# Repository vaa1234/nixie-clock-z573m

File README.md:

Nixie Clock on z573m tubes, hv5222 and raspberry pi.

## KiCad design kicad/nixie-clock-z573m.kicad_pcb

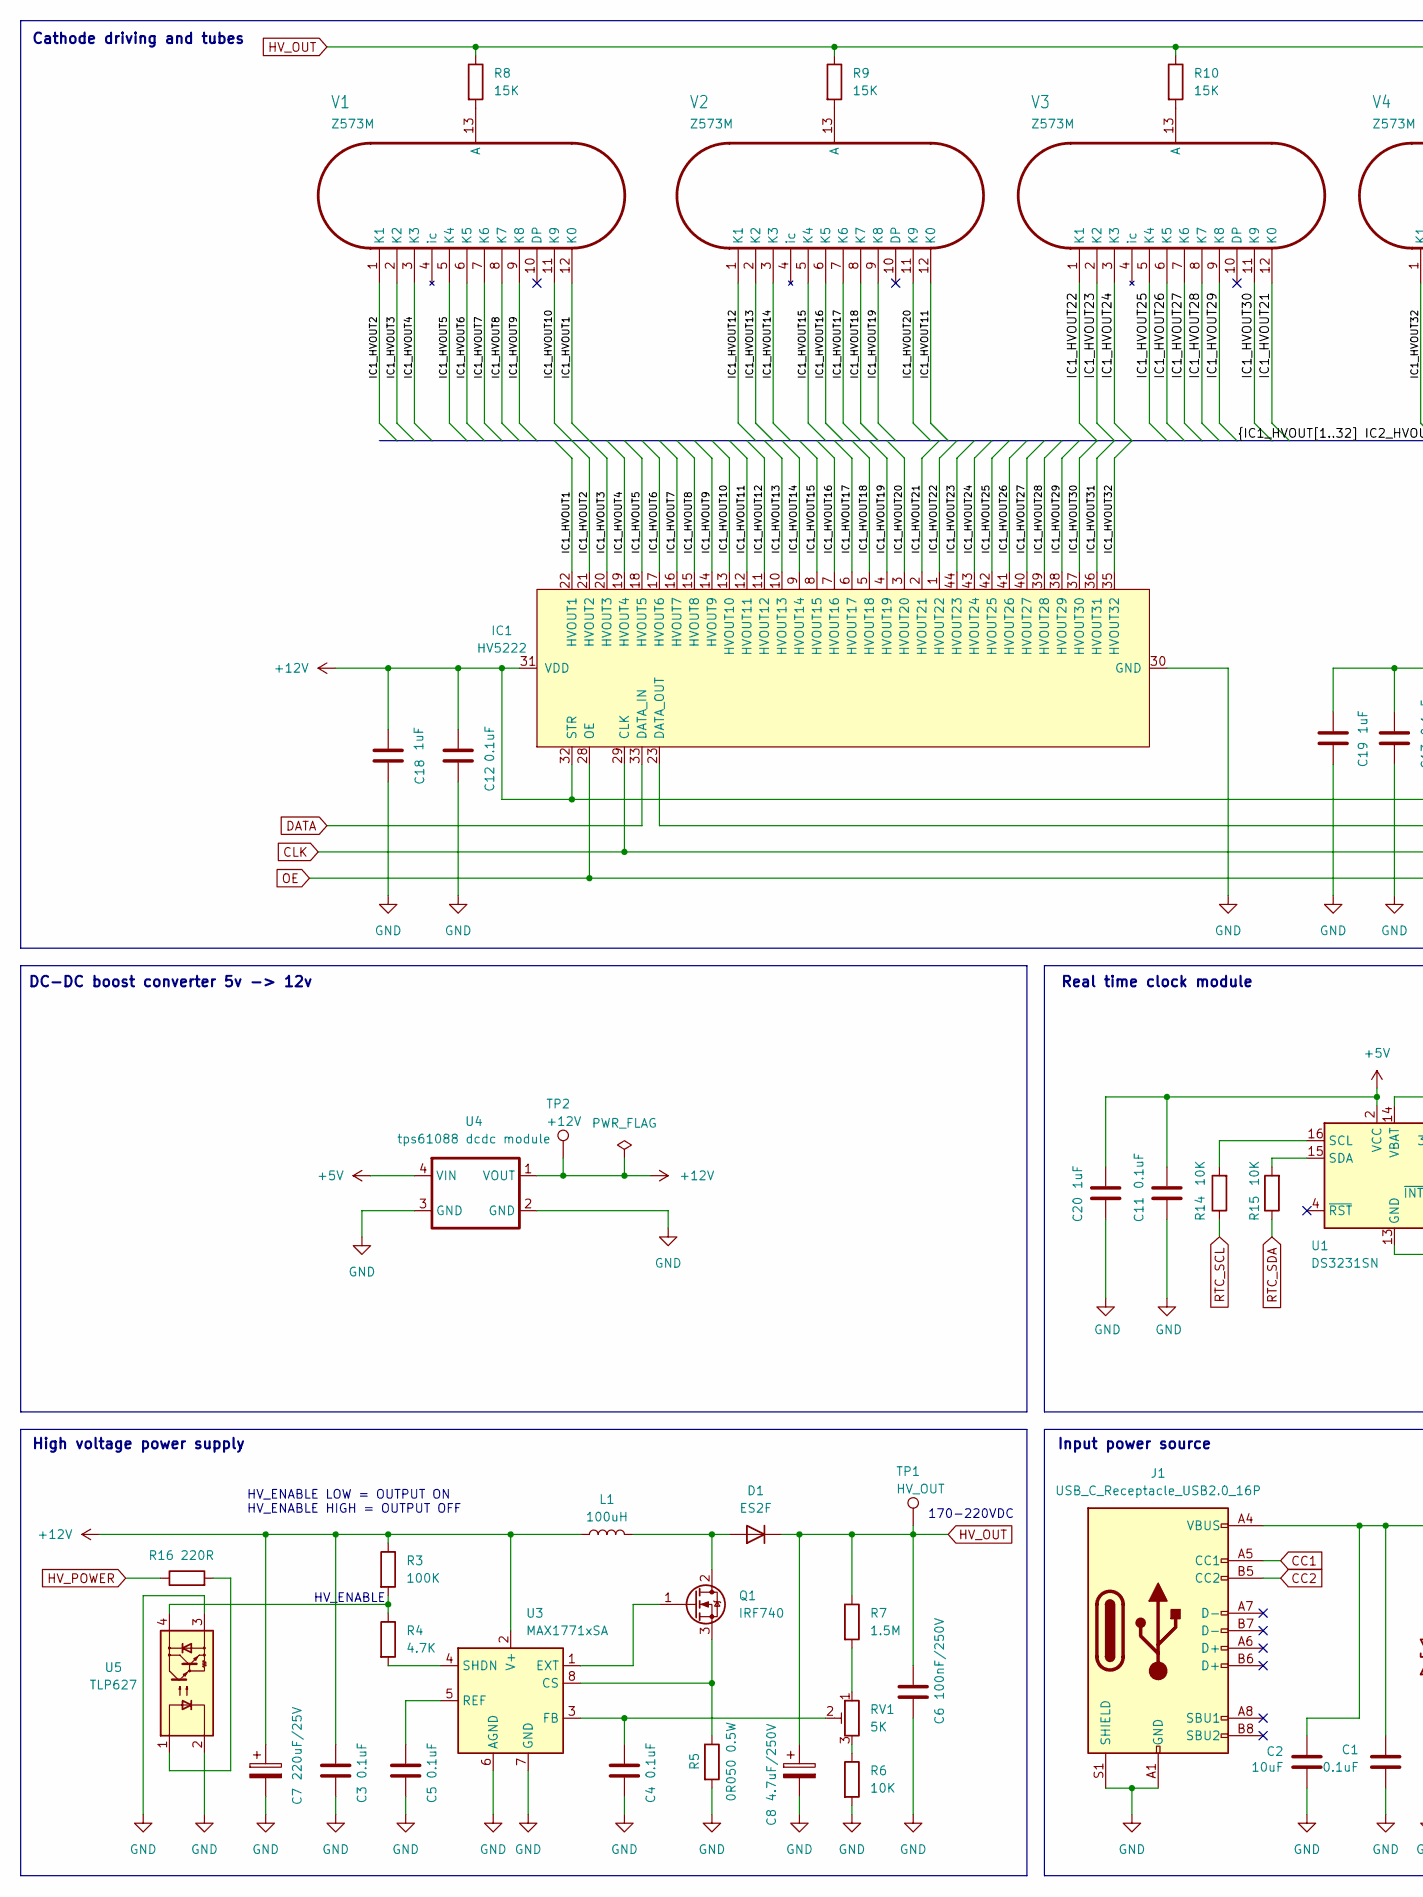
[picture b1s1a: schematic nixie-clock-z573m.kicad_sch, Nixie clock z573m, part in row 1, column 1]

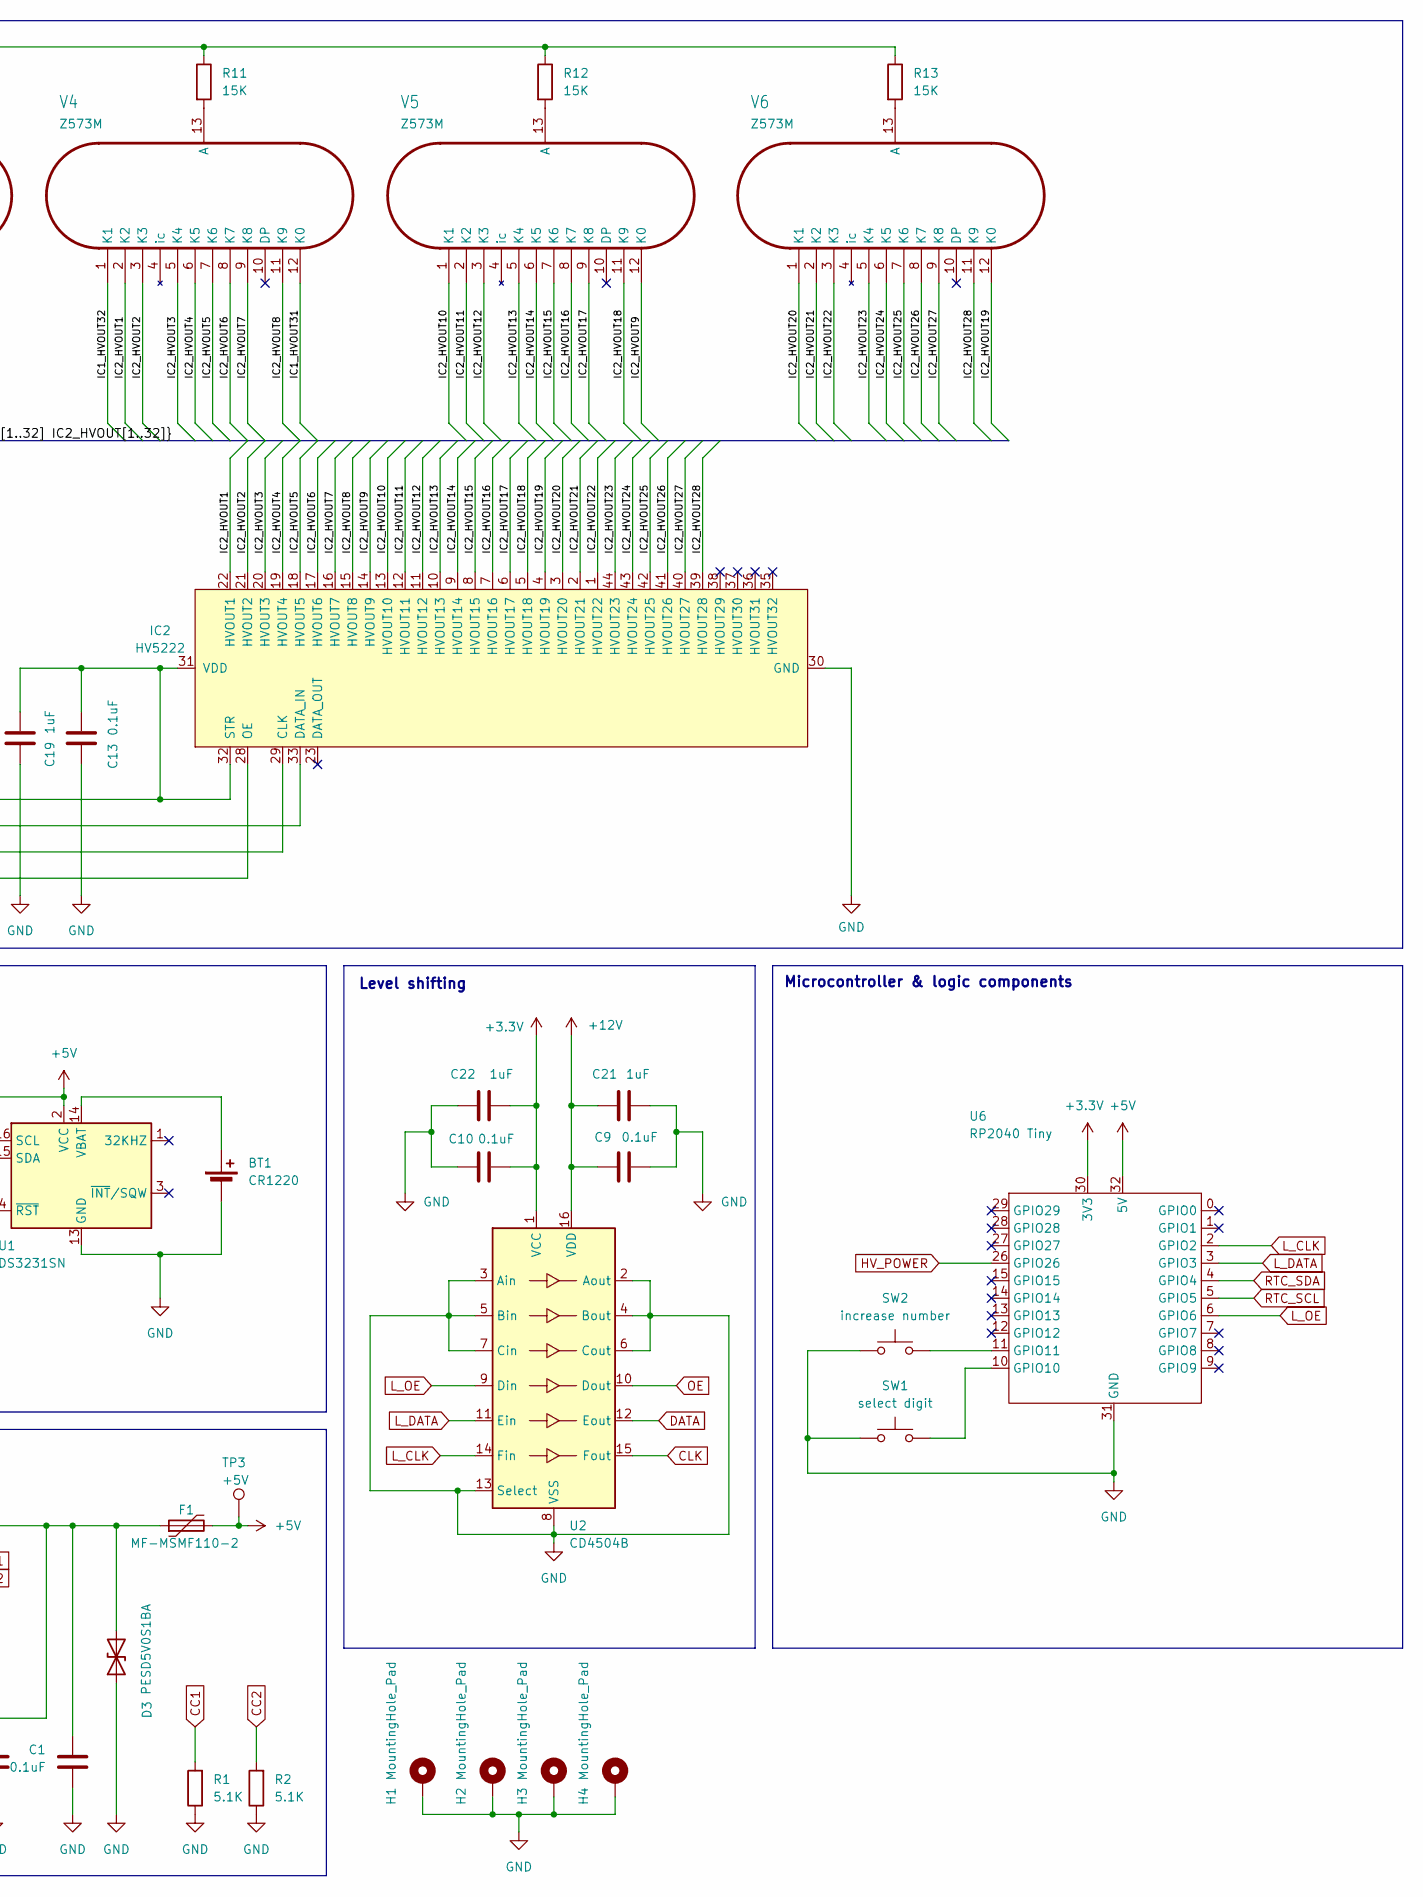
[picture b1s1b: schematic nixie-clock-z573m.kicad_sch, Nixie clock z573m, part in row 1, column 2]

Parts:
BT1: CR1220; BatteryHolder_Keystone_3000_1x12mm
C1, C3, C4, C5, C9, C10, C11, C12, C13: 0.1uF; C_0402_1005Metric_Pad0.74x0.62mm_HandSolder
C2: 10uF; C_0805_2012Metric_Pad1.18x1.45mm_HandSolder
C6: 100nF/250V; C_1206_3216Metric_Pad1.33x1.80mm_HandSolder
C7: 220uF/25V; CP_Elec_8x10.5
C8: 4.7uF/250V; CP_Elec_8x10
C18, C19, C20, C21, C22: 1uF; C_0201_0603Metric_Pad0.64x0.40mm_HandSolder
D1: ES2F; D_SMB_Handsoldering
D3: PESD5V0S1BA; D_SOD-323
F1: MF-MSMF110-2; Fuse_1812_4532Metric_Pad1.30x3.40mm_HandSolder
H1, H2, H3, H4: MountingHole_Pad; MountingHole_3mm_Pad_Via
IC1, IC2: HV5222; PQFP-44_10x10mm_P0.8mm
J1: USB_C_Receptacle_USB2.0_16P; USB_C_Receptacle_GCT_USB4105-xx-A_16P_TopMnt_Horizontal
L1: 100uH; L_12x12mm_H8mm
Q1: IRF740; TO-252-2
R1, R2: 5.1K; R_0402_1005Metric_Pad0.72x0.64mm_HandSolder
R3: 100K; R_0603_1608Metric_Pad0.98x0.95mm_HandSolder
R4: 4.7K; R_0603_1608Metric_Pad0.98x0.95mm_HandSolder
R5: 0R050 0.5W; R_2010_5025Metric_Pad1.40x2.65mm_HandSolder
R6: 10K; R_0603_1608Metric_Pad0.98x0.95mm_HandSolder
R7: 1.5M; R_0603_1608Metric_Pad0.98x0.95mm_HandSolder
R8, R9, R10, R11, R12, R13: 15K; R_1206_3216Metric_Pad1.30x1.75mm_HandSolder
R14, R15: 10K; R_0201_0603Metric_Pad0.64x0.40mm_HandSolder
R16: 220R; R_0603_1608Metric_Pad0.98x0.95mm_HandSolder
RV1: 5K; Potentiometer_Bourns_3224W_Vertical
SW1: select digit; SW_Tactile_SPST_Angled_PTS645Vx83-2LFS
SW2: increase number; SW_Tactile_SPST_Angled_PTS645Vx83-2LFS
TP1: HV_OUT; TestPoint_Pad_D1.0mm
TP2: +12V; TestPoint_Pad_D1.0mm
TP3: +5V; TestPoint_Pad_D1.0mm
U1: DS3231SN; SOIC-16W_7.5x10.3mm_P1.27mm
U2: CD4504B; SOIC-16W_5.3x10.2mm_P1.27mm
U3: MAX1771xSA; SO-8_3.9x4.9mm_P1.27mm
U4: tps61088 dcdc module; tps61088_module
U5: TLP627; DIP-4_W7.62mm_Socket
U6: RP2040 Tiny; RP2040-Tiny_SMD
V1, V2, V3, V4, V5, V6: Z573M; Z573M_SMD

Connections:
+3.3V: C10.2, C22.2, U2.1 (VCC), U6.30 (3V3)
+5V: C11.1, C20.1, F1.2, TP3.1, U1.2 (VCC), U4.4 (VIN), U6.32 (5V)
+12V: C3.1, C7.1, C9.1, C12.1, C13.1, C18.1, C19.1, C21.1, IC1.31 (VDD), IC1.32 (STR), IC2.31 (VDD), IC2.32 (STR), L1.1, R3.1, TP2.1, U2.16 (VDD), U3.2 (V+), U4.1 (VOUT)
/IC1_HVOUT1: IC1.22 (HVOUT1), V1.12 (K0)
/IC1_HVOUT2: IC1.21 (HVOUT2), V1.1 (K1)
/IC1_HVOUT3: IC1.20 (HVOUT3), V1.2 (K2)
/IC1_HVOUT4: IC1.19 (HVOUT4), V1.3 (K3)
/IC1_HVOUT5: IC1.18 (HVOUT5), V1.5 (K4)
/IC1_HVOUT6: IC1.17 (HVOUT6), V1.6 (K5)
/IC1_HVOUT7: IC1.16 (HVOUT7), V1.7 (K6)
/IC1_HVOUT8: IC1.15 (HVOUT8), V1.8 (K7)
/IC1_HVOUT9: IC1.14 (HVOUT9), V1.9 (K8)
/IC1_HVOUT10: IC1.13 (HVOUT10), V1.11 (K9)
/IC1_HVOUT11: IC1.12 (HVOUT11), V2.12 (K0)
/IC1_HVOUT12: IC1.11 (HVOUT12), V2.1 (K1)
/IC1_HVOUT13: IC1.10 (HVOUT13), V2.2 (K2)
/IC1_HVOUT14: IC1.9 (HVOUT14), V2.3 (K3)
/IC1_HVOUT15: IC1.8 (HVOUT15), V2.5 (K4)
/IC1_HVOUT16: IC1.7 (HVOUT16), V2.6 (K5)
/IC1_HVOUT17: IC1.6 (HVOUT17), V2.7 (K6)
/IC1_HVOUT18: IC1.5 (HVOUT18), V2.8 (K7)
/IC1_HVOUT19: IC1.4 (HVOUT19), V2.9 (K8)
/IC1_HVOUT20: IC1.3 (HVOUT20), V2.11 (K9)
/IC1_HVOUT21: IC1.2 (HVOUT21), V3.12 (K0)
/IC1_HVOUT22: IC1.1 (HVOUT22), V3.1 (K1)
/IC1_HVOUT23: IC1.44 (HVOUT23), V3.2 (K2)
/IC1_HVOUT24: IC1.43 (HVOUT24), V3.3 (K3)
/IC1_HVOUT25: IC1.42 (HVOUT25), V3.5 (K4)
/IC1_HVOUT26: IC1.41 (HVOUT26), V3.6 (K5)
/IC1_HVOUT27: IC1.40 (HVOUT27), V3.7 (K6)
/IC1_HVOUT28: IC1.39 (HVOUT28), V3.8 (K7)
/IC1_HVOUT29: IC1.38 (HVOUT29), V3.9 (K8)
/IC1_HVOUT30: IC1.37 (HVOUT30), V3.11 (K9)
/IC1_HVOUT31: IC1.36 (HVOUT31), V4.12 (K0)
/IC1_HVOUT32: IC1.35 (HVOUT32), V4.1 (K1)
/IC2_HVOUT1: IC2.22 (HVOUT1), V4.2 (K2)
/IC2_HVOUT2: IC2.21 (HVOUT2), V4.3 (K3)
/IC2_HVOUT3: IC2.20 (HVOUT3), V4.5 (K4)
/IC2_HVOUT4: IC2.19 (HVOUT4), V4.6 (K5)
/IC2_HVOUT5: IC2.18 (HVOUT5), V4.7 (K6)
/IC2_HVOUT6: IC2.17 (HVOUT6), V4.8 (K7)
/IC2_HVOUT7: IC2.16 (HVOUT7), V4.9 (K8)
/IC2_HVOUT8: IC2.15 (HVOUT8), V4.11 (K9)
/IC2_HVOUT9: IC2.14 (HVOUT9), V5.12 (K0)
/IC2_HVOUT10: IC2.13 (HVOUT10), V5.1 (K1)
/IC2_HVOUT11: IC2.12 (HVOUT11), V5.2 (K2)
/IC2_HVOUT12: IC2.11 (HVOUT12), V5.3 (K3)
/IC2_HVOUT13: IC2.10 (HVOUT13), V5.5 (K4)
/IC2_HVOUT14: IC2.9 (HVOUT14), V5.6 (K5)
/IC2_HVOUT15: IC2.8 (HVOUT15), V5.7 (K6)
/IC2_HVOUT16: IC2.7 (HVOUT16), V5.8 (K7)
/IC2_HVOUT17: IC2.6 (HVOUT17), V5.9 (K8)
/IC2_HVOUT18: IC2.5 (HVOUT18), V5.11 (K9)
/IC2_HVOUT19: IC2.4 (HVOUT19), V6.12 (K0)
/IC2_HVOUT20: IC2.3 (HVOUT20), V6.1 (K1)
/IC2_HVOUT21: IC2.2 (HVOUT21), V6.2 (K2)
/IC2_HVOUT22: IC2.1 (HVOUT22), V6.3 (K3)
/IC2_HVOUT23: IC2.44 (HVOUT23), V6.5 (K4)
/IC2_HVOUT24: IC2.43 (HVOUT24), V6.6 (K5)
/IC2_HVOUT25: IC2.42 (HVOUT25), V6.7 (K6)
/IC2_HVOUT26: IC2.41 (HVOUT26), V6.8 (K7)
/IC2_HVOUT27: IC2.40 (HVOUT27), V6.9 (K8)
/IC2_HVOUT28: IC2.39 (HVOUT28), V6.11 (K9)
CC1: J1.A5 (CC1), R1.2
CC2: J1.B5 (CC2), R2.2
CLK: IC1.29 (CLK), IC2.29 (CLK), U2.15 (Fout)
DATA: IC1.33 (DATA_IN), U2.12 (Eout)
GND: BT1.2 (-), C1.2, C2.1, C3.2, C4.2, C5.2, C6.2, C7.2, C8.2, C9.2, C10.1, C11.2, C12.2, C13.2, C18.2, C19.2, C20.2, C21.2, C22.1, D3.1 (A1), H1.1, H2.1, H3.1, H4.1, IC1.30 (GND), IC2.30 (GND), J1.A1 (GND), J1.A12 (GND), J1.B1 (GND), J1.B12 (GND), J1.S1 (SHIELD), R1.1, R2.1, R5.2, R6.2, SW1.1, SW2.1, U1.5 (GND), U1.6 (GND), U1.7 (GND), U1.8 (GND), U1.9 (GND), U1.10 (GND), U1.11 (GND), U1.12 (GND), U1.13 (GND), U2.2 (Aout), U2.3 (Ain), U2.4 (Bout), U2.5 (Bin), U2.6 (Cout), U2.7 (Cin), U2.8 (VSS), U2.13 (Select), U3.6 (AGND), U3.7 (GND), U4.2 (GND), U4.3 (GND), U5.2, U5.3, U6.31 (GND)
HV_OUT: C6.1, C8.1, D1.1 (K), R7.1, R8.1, R9.1, R10.1, R11.1, R12.1, R13.1, TP1.1
HV_POWER: R16.1, U6.26 (GPIO26)
L_CLK: U2.14 (Fin), U6.2 (GPIO2)
L_DATA: U2.11 (Ein), U6.3 (GPIO3)
L_OE: U2.9 (Din), U6.6 (GPIO6)
unnamed: BT1.1 (+), U1.14 (VBAT)
unnamed: D1.2 (A), L1.2, Q1.2 (D)
unnamed: C1.1, C2.2, D3.2 (A2), F1.1, J1.A4 (VBUS), J1.A9 (VBUS), J1.B4 (VBUS), J1.B9 (VBUS)
unnamed: IC1.23 (DATA_OUT), IC2.33 (DATA_IN)
unnamed: Q1.1 (G), U3.1 (EXT)
unnamed: Q1.3 (S), R5.1, U3.8 (CS)
unnamed: R3.2, R4.1, U5.4
unnamed: R6.1, RV1.3
unnamed: R7.2, RV1.1
unnamed: R16.2, U5.1
unnamed: R14.2, U1.16 (SCL)
unnamed: R15.2, U1.15 (SDA)
unnamed: C4.1, RV1.2, U3.3 (FB)
unnamed: C5.1, U3.5 (REF)
unnamed: R4.2, U3.4 (SHDN)
unnamed: SW1.2, U6.10 (GPIO10)
unnamed: SW2.2, U6.11 (GPIO11)
unnamed: R8.2, V1.13 (A)
unnamed: R9.2, V2.13 (A)
unnamed: R10.2, V3.13 (A)
unnamed: R11.2, V4.13 (A)
unnamed: R12.2, V5.13 (A)
unnamed: R13.2, V6.13 (A)
OE: IC1.28 (OE), IC2.28 (OE), U2.10 (Dout)
RTC_SCL: R14.1, U6.5 (GPIO5)
RTC_SDA: R15.1, U6.4 (GPIO4)

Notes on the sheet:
Level shifting
High voltage power supply
Real time clock module
HV_ENABLE LOW = OUTPUT ON HV_ENABLE HIGH = OUTPUT OFF
Input power source
Microcontroller & logic components
Cathode driving and tubes
170-220VDC
HV_ENABLE
DC-DC boost converter 5v -> 12v

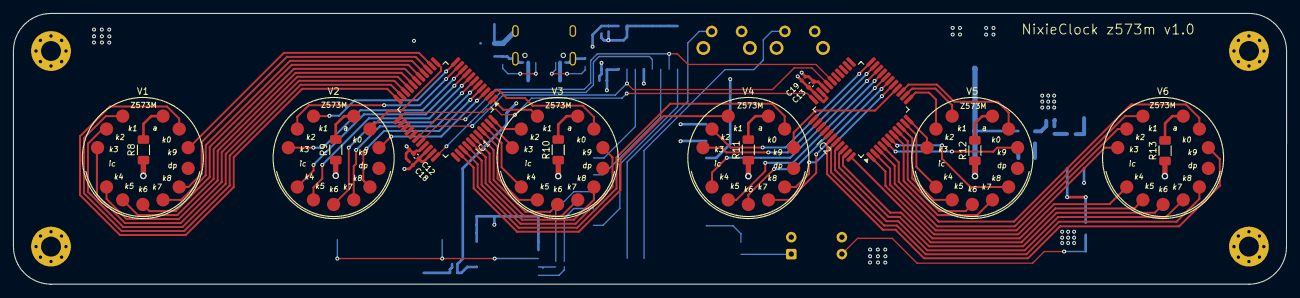
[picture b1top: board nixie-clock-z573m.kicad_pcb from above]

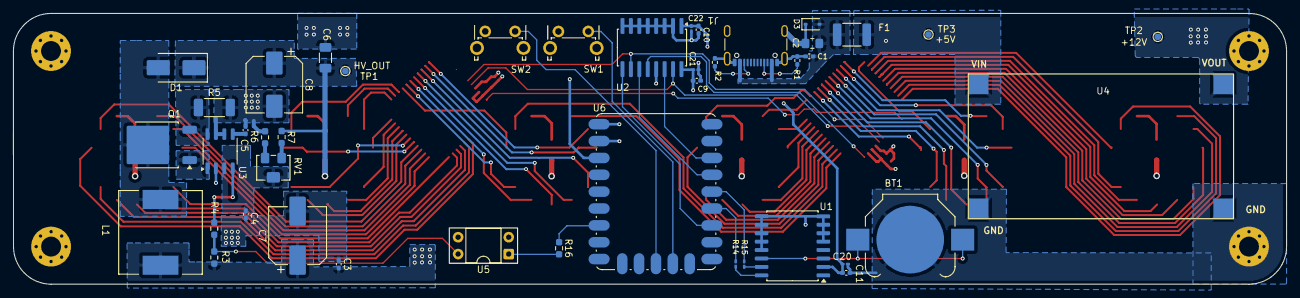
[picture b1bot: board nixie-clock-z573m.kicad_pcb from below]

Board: 4 copper layers, 191.8 x 40.8 mm, 65 parts (43 on the bottom side), 99 nets.

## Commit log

2025-09-12 initial release
